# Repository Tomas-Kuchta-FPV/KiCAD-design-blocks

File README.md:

# KiCAD-design-blocks
Design blocks for your basic KiCAD needs. The aim for them is to be useful, versatile, universal, standardized, FOSS and leverage the new features in KiCAD.  

Here are the things that my blocks should be:
- Modular
- Easy to implement
- "Standardized"
- Manufacturer and LCSC part number

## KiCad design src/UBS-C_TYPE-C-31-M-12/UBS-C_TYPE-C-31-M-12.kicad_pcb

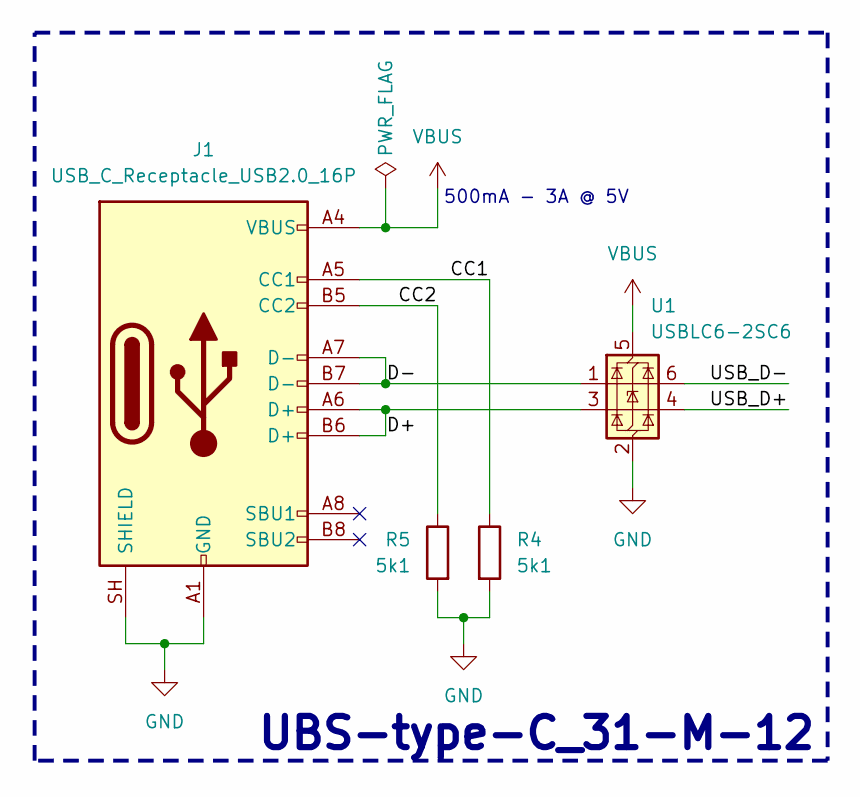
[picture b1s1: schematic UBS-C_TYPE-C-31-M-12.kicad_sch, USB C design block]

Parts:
J1: USB_C_Receptacle_USB2.0_16P; USB_C_Receptacle_HRO_TYPE-C-31-M-12; LCSC C165948
R4, R5: 5k1; R_0805_2012Metric_Pad1.20x1.40mm_HandSolder; LCSC C84375
U1: USBLC6-2SC6; SOT-23-6; LCSC C2827654

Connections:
/CC1: J1.A5 (CC1), R4.1
/CC2: J1.B5 (CC2), R5.1
/D+: J1.A6 (D+), J1.B6 (D+), U1.3 (I/O2)
/D-: J1.A7 (D-), J1.B7 (D-), U1.1 (I/O1)
/USB_D+: U1.4 (I/O2)
/USB_D-: U1.6 (I/O1)
GND: J1.A1 (GND), J1.A12 (GND), J1.B1 (GND), J1.B12 (GND), J1.SH (SHIELD), R4.2, R5.2, U1.2 (GND)
VBUS: J1.A4 (VBUS), J1.A9 (VBUS), J1.B4 (VBUS), J1.B9 (VBUS), U1.5 (VBUS)

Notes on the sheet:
500mA - 3A @ 5V
UBS-type-C_31-M-12

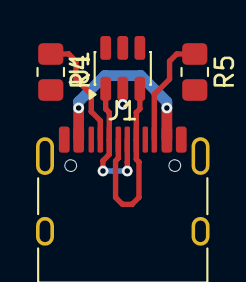
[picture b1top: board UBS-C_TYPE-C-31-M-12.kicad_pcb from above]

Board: 2 copper layers, 4 parts (0 on the bottom side), 6 nets.
